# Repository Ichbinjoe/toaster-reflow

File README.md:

# Toaster Reflow

This board is a Raspberry Pi hat designed to be hooked up to a toaster oven to
reflow circuit boards. This board features:

+ AC Relay for turning on and off the toaster oven
+ Two thermocouple inputs
+ A servo connection for optional door servo
+ A buzzer for notifications

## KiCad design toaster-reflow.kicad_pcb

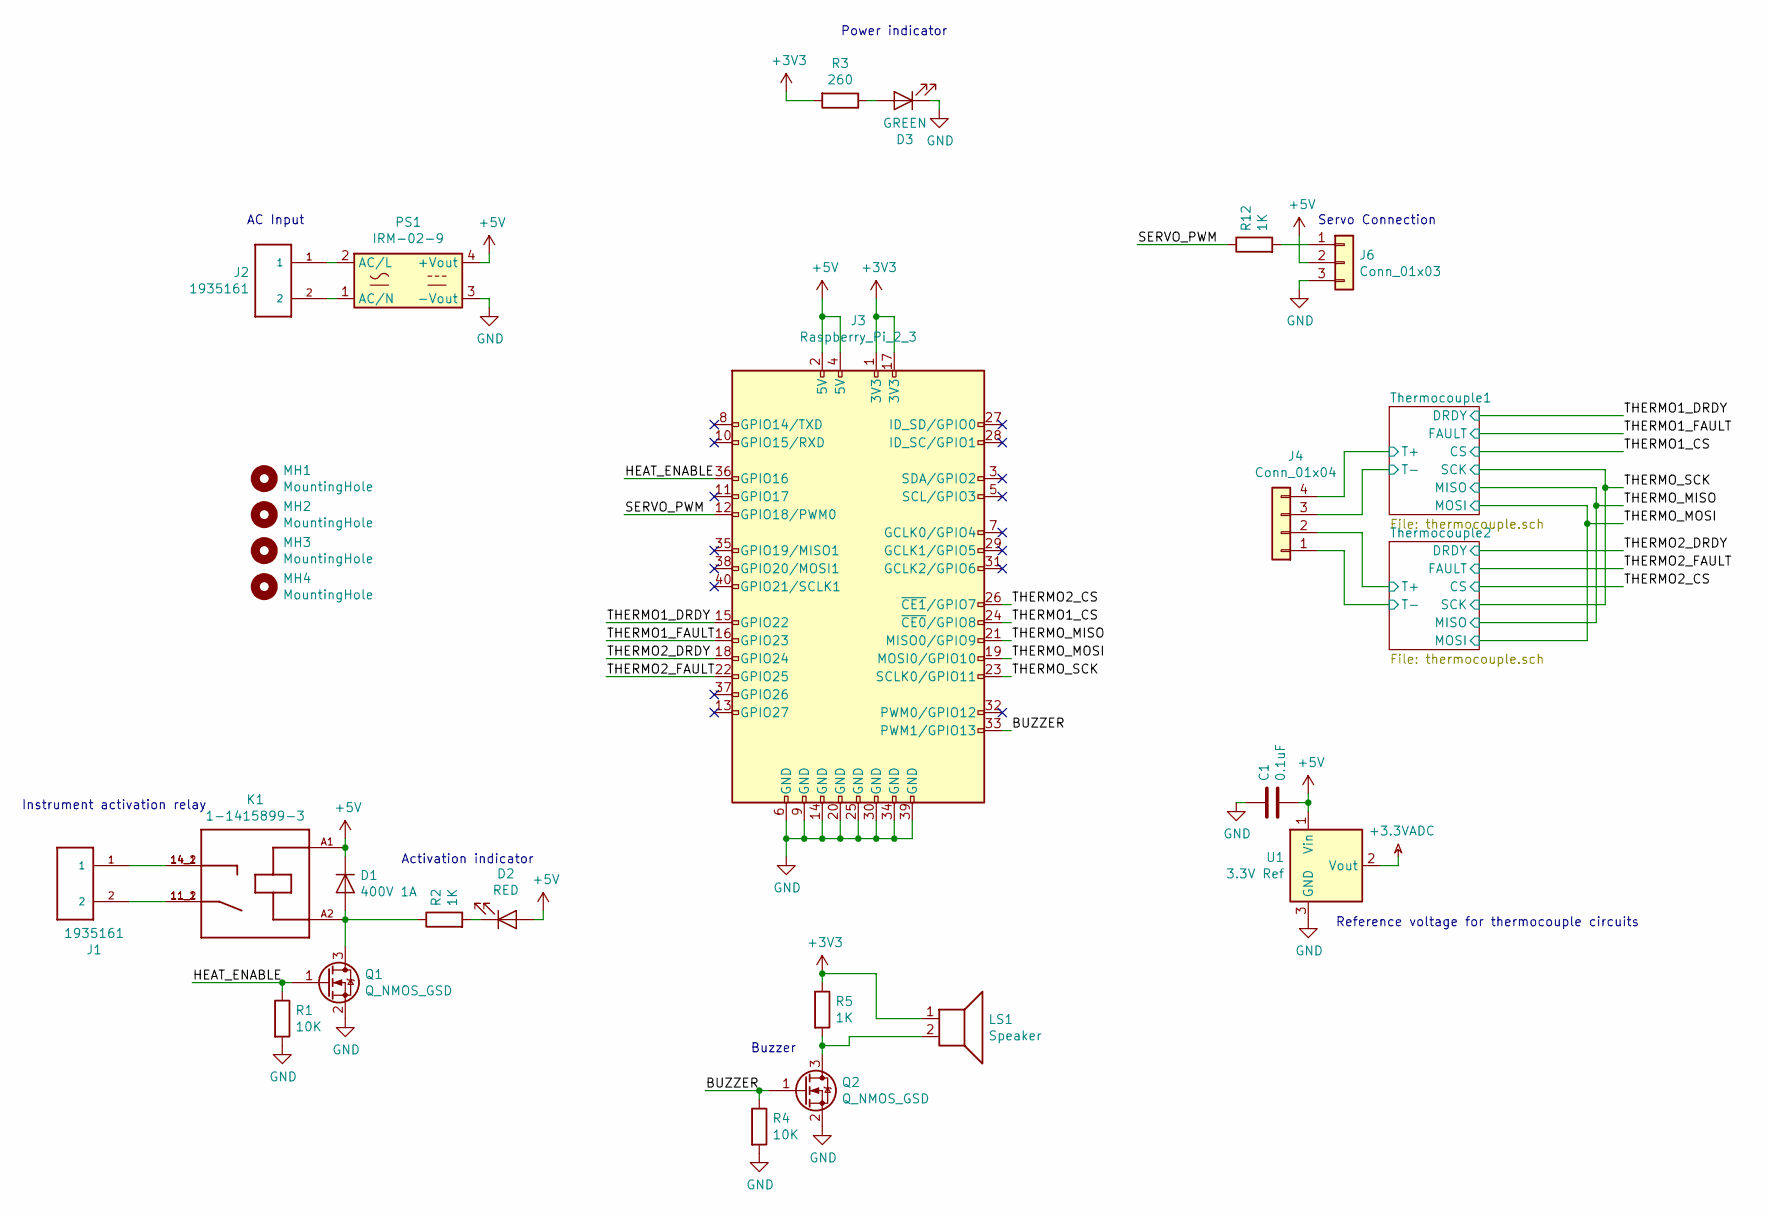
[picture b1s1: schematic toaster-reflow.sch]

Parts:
C1: 0.1uF; C_0603_1608Metric; DigikeyPartNumber 1276-1258-1-ND
D1: 400V 1A; D_SMA; DigikeyPartNumber 1655-1504-1-ND
D2: RED; D_0603_1608Metric; DigikeyPartNumber 732-4978-1-ND
D3: GREEN; D_0603_1608Metric; DigikeyPartNumber 732-4980-1-ND
J1, J2: 1935161; PHOENIX_1935161; DigikeyPartNumber 277-1667-ND
J3: Raspberry_Pi_2_3; PinHeader_2x20_P2.54mm_Vertical; DigikeyPartNumber S9200-ND
J4: Conn_01x04; 1990025; DigikeyPartNumber 277-1796-ND
J6: Conn_01x03; PinSocket_1x03_P2.54mm_Vertical; DigikeyPartNumber 732-5316-ND
K1: 1-1415899-3; RELAY_1-1415899-3; DigikeyPartNumber PB1267-ND
LS1: Speaker; PS12; DigikeyPartNumber 445-2525-1-ND
MH1, MH2, MH3, MH4: MountingHole; MountingHole_2.7mm_M2.5; DigikeyPartNumber 732-12923-ND
PS1: IRM-02-9; IRM-15-5; DigikeyPartNumber 1866-3037-ND
Q1, Q2: Q_NMOS_GSD; SC-59; DigikeyPartNumber RK7002BMT116CT-ND
R1, R4: 10K; R_0603_1608Metric; DigikeyPartNumber P10KGCT-ND
R2, R5, R12: 1K; R_0603_1608Metric; DigikeyPartNumber RHM1.0KDCT-ND
R3: 260; R_0603_1608Metric; DigikeyPartNumber P261HCT-ND
U1: 3.3V Ref; SOT-23; DigikeyPartNumber NCP51460SN33T1GOSCT-ND

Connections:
+3.3VADC: U1.2 (Vout); also elsewhere on the board
+3V3: J3.1 (3V3), J3.17 (3V3), LS1.1, R3.2, R5.1; also elsewhere on the board
+5V: C1.2, D1.1 (K), D2.2 (A), J3.2 (5V), J3.4 (5V), J6.2, K1.A1 (A2), PS1.4 (+Vout), U1.1 (Vin)
/BUZZER: J3.33 (PWM1/GPIO13), Q2.1 (G), R4.1
/HEAT_ENABLE: J3.36 (GPIO16), Q1.1 (G), R1.1
/SERVO_PWM: J3.12 (GPIO18/PWM0), R12.1
/THERMO1_CS: J3.24 (~CE0~/GPIO8); also elsewhere on the board
/THERMO1_DRDY: J3.15 (GPIO22); also elsewhere on the board
/THERMO1_FAULT: J3.16 (GPIO23); also elsewhere on the board
/THERMO2_CS: J3.26 (~CE1~/GPIO7); also elsewhere on the board
/THERMO2_DRDY: J3.18 (GPIO24); also elsewhere on the board
/THERMO2_FAULT: J3.22 (GPIO25); also elsewhere on the board
/THERMO_MISO: J3.21 (MISO0/GPIO9); also elsewhere on the board
/THERMO_MOSI: J3.19 (MOSI0/GPIO10); also elsewhere on the board
/THERMO_SCK: J3.23 (SCLK0/GPIO11); also elsewhere on the board
/Thermocouple1/T+: J4.4; also elsewhere on the board
/Thermocouple1/T-: J4.3; also elsewhere on the board
/Thermocouple2/T+: J4.2; also elsewhere on the board
/Thermocouple2/T-: J4.1; also elsewhere on the board
GND: C1.1, D3.1 (K), J3.6 (GND), J3.9 (GND), J3.14 (GND), J3.20 (GND), J3.25 (GND), J3.30 (GND), J3.34 (GND), J3.39 (GND), J6.3, PS1.3 (-Vout), Q1.2 (S), Q2.2 (S), R1.2, R4.2, U1.3 (GND); also elsewhere on the board
unnamed: D1.2 (A), K1.A2 (A1), Q1.3 (D), R2.1
unnamed: D2.1 (K), R2.2
unnamed: D3.2 (A), R3.1
unnamed: J1.1, K1.14_1 (14), K1.14_2 (14)
unnamed: J1.2, K1.11_1 (11), K1.11_2 (11)
unnamed: J2.1, PS1.2 (AC/L)
unnamed: J2.2, PS1.1 (AC/N)
unnamed: J6.1, R12.2
unnamed: LS1.2, Q2.3 (D), R5.2

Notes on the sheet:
Power indicator
Activation indicator
Instrument activation relay
Servo Connection
Reference voltage for thermocouple circuits
Buzzer
AC Input

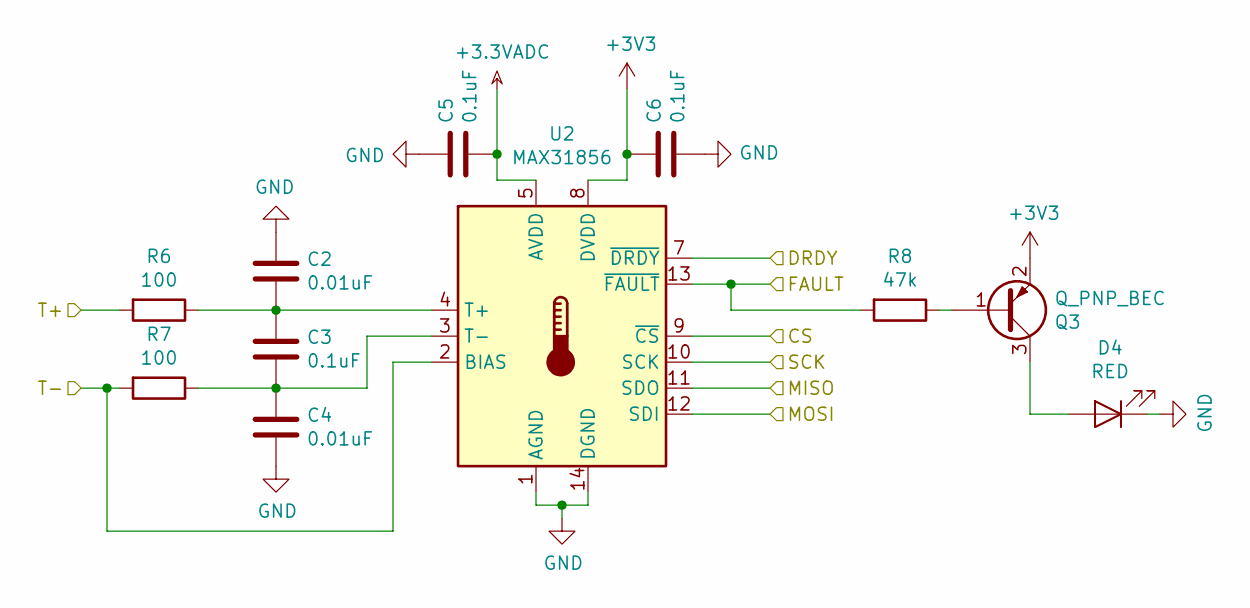
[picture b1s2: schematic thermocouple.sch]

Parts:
C2, C4: 0.01uF; C_0603_1608Metric; DigikeyPartNumber 1276-1921-1-ND
C3, C5, C6: 0.1uF; C_0603_1608Metric; DigikeyPartNumber 1276-1258-1-ND
D4: RED; D_0603_1608Metric; DigikeyPartNumber 732-4978-1-ND
Q3: Q_PNP_BEC; SC-59; DigikeyPartNumber MMBT3906-FDICT-ND
R6, R7: 100; R_0603_1608Metric; DigikeyPartNumber P100HCT-ND
R8: 47k; R_0603_1608Metric; DigikeyPartNumber P47.0KHCT-ND
U2: MAX31856; TSSOP-14_4.4x5mm_P0.65mm; DigikeyPartNumber MAX31856MUD+-ND

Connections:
+3.3VADC: C5.2, U2.5 (AVDD); also elsewhere on the board
+3V3: C6.1, Q3.2 (E), U2.8 (DVDD); also elsewhere on the board
/THERMO1_CS: U2.9 (~CS); also elsewhere on the board
/THERMO1_DRDY: U2.7 (~DRDY); also elsewhere on the board
/THERMO1_FAULT: R8.2, U2.13 (~FAULT); also elsewhere on the board
/THERMO_MISO: U2.11 (SDO); also elsewhere on the board
/THERMO_MOSI: U2.12 (SDI); also elsewhere on the board
/THERMO_SCK: U2.10 (SCK); also elsewhere on the board
/Thermocouple1/T+: R6.2; also elsewhere on the board
/Thermocouple1/T-: R7.2, U2.2 (BIAS); also elsewhere on the board
GND: C2.1, C4.2, C5.1, C6.2, D4.1 (K), U2.1 (AGND), U2.14 (DGND); also elsewhere on the board
unnamed: C2.2, C3.1, R6.1, U2.4 (T+)
unnamed: C3.2, C4.1, R7.1, U2.3 (T-)
unnamed: D4.2 (A), Q3.3 (C)
unnamed: Q3.1 (B), R8.1

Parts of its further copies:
C7, C9: 0.01uF; C_0603_1608Metric; DigikeyPartNumber 1276-1921-1-ND
C8, C10, C11: 0.1uF; C_0603_1608Metric; DigikeyPartNumber 1276-1258-1-ND
D5: RED; D_0603_1608Metric; DigikeyPartNumber 732-4978-1-ND
Q4: Q_PNP_BEC; SC-59; DigikeyPartNumber MMBT3906-FDICT-ND
R9, R10: 100; R_0603_1608Metric; DigikeyPartNumber P100HCT-ND
R11: 47k; R_0603_1608Metric; DigikeyPartNumber P47.0KHCT-ND
U3: MAX31856; TSSOP-14_4.4x5mm_P0.65mm; DigikeyPartNumber MAX31856MUD+-ND

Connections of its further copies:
+3.3VADC: C10.2, U3.5 (AVDD); also elsewhere on the board
+3V3: C11.1, Q4.2 (E), U3.8 (DVDD); also elsewhere on the board
/THERMO2_CS: U3.9 (~CS); also elsewhere on the board
/THERMO2_DRDY: U3.7 (~DRDY); also elsewhere on the board
/THERMO2_FAULT: R11.2, U3.13 (~FAULT); also elsewhere on the board
/THERMO_MISO: U3.11 (SDO); also elsewhere on the board
/THERMO_MOSI: U3.12 (SDI); also elsewhere on the board
/THERMO_SCK: U3.10 (SCK); also elsewhere on the board
/Thermocouple2/T+: R9.2; also elsewhere on the board
/Thermocouple2/T-: R10.2, U3.2 (BIAS); also elsewhere on the board
GND: C7.1, C9.2, C10.1, C11.2, D5.1 (K), U3.1 (AGND), U3.14 (DGND); also elsewhere on the board
unnamed: C7.2, C8.1, R9.1, U3.4 (T+)
unnamed: C8.2, C9.1, R10.1, U3.3 (T-)
unnamed: D5.2 (A), Q4.3 (C)
unnamed: Q4.1 (B), R11.1

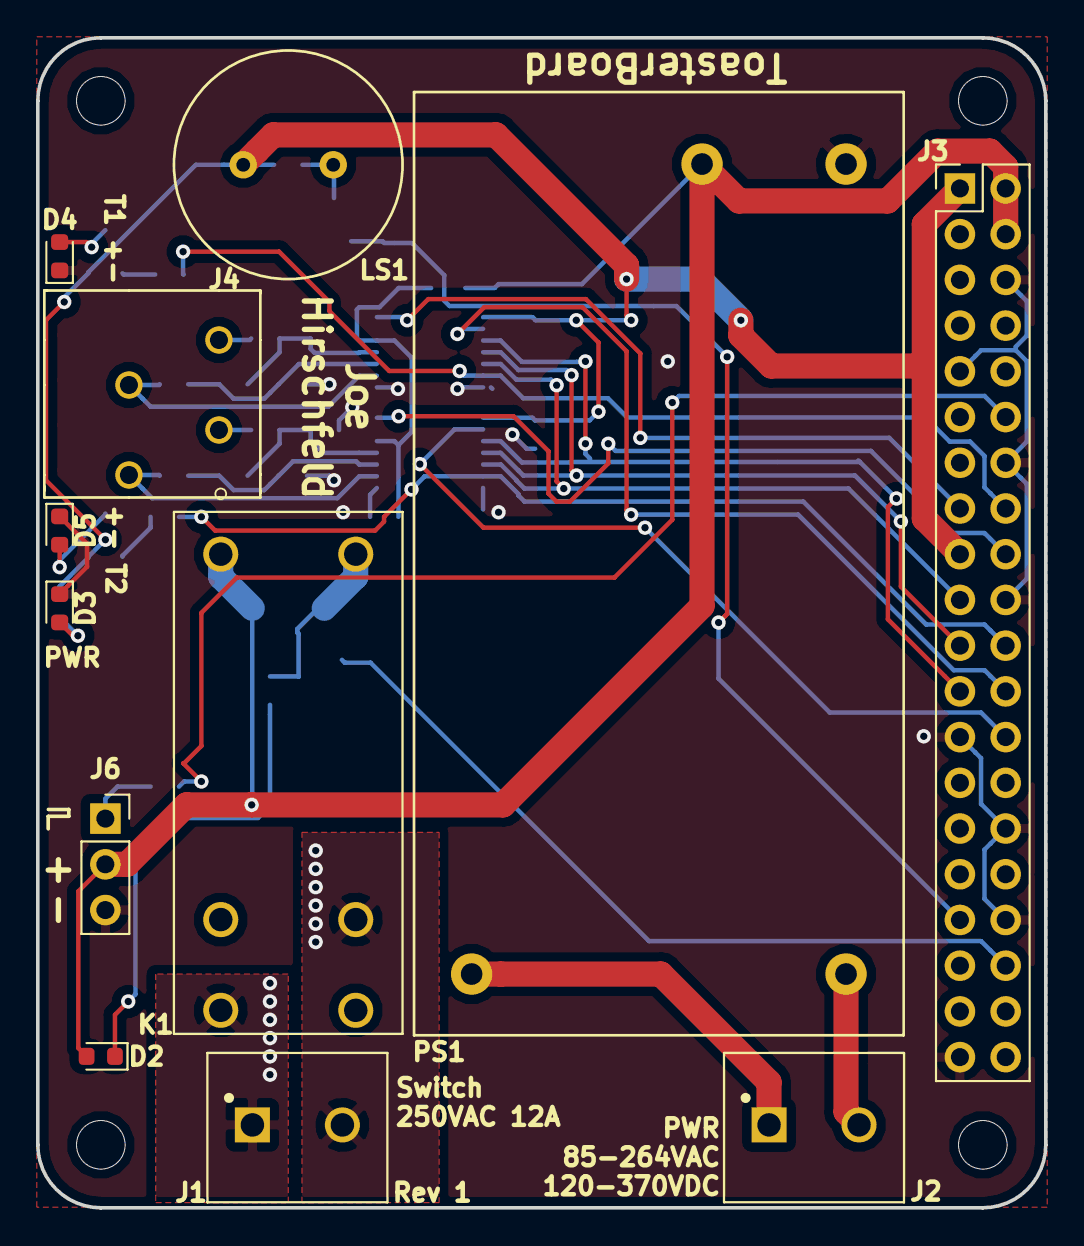
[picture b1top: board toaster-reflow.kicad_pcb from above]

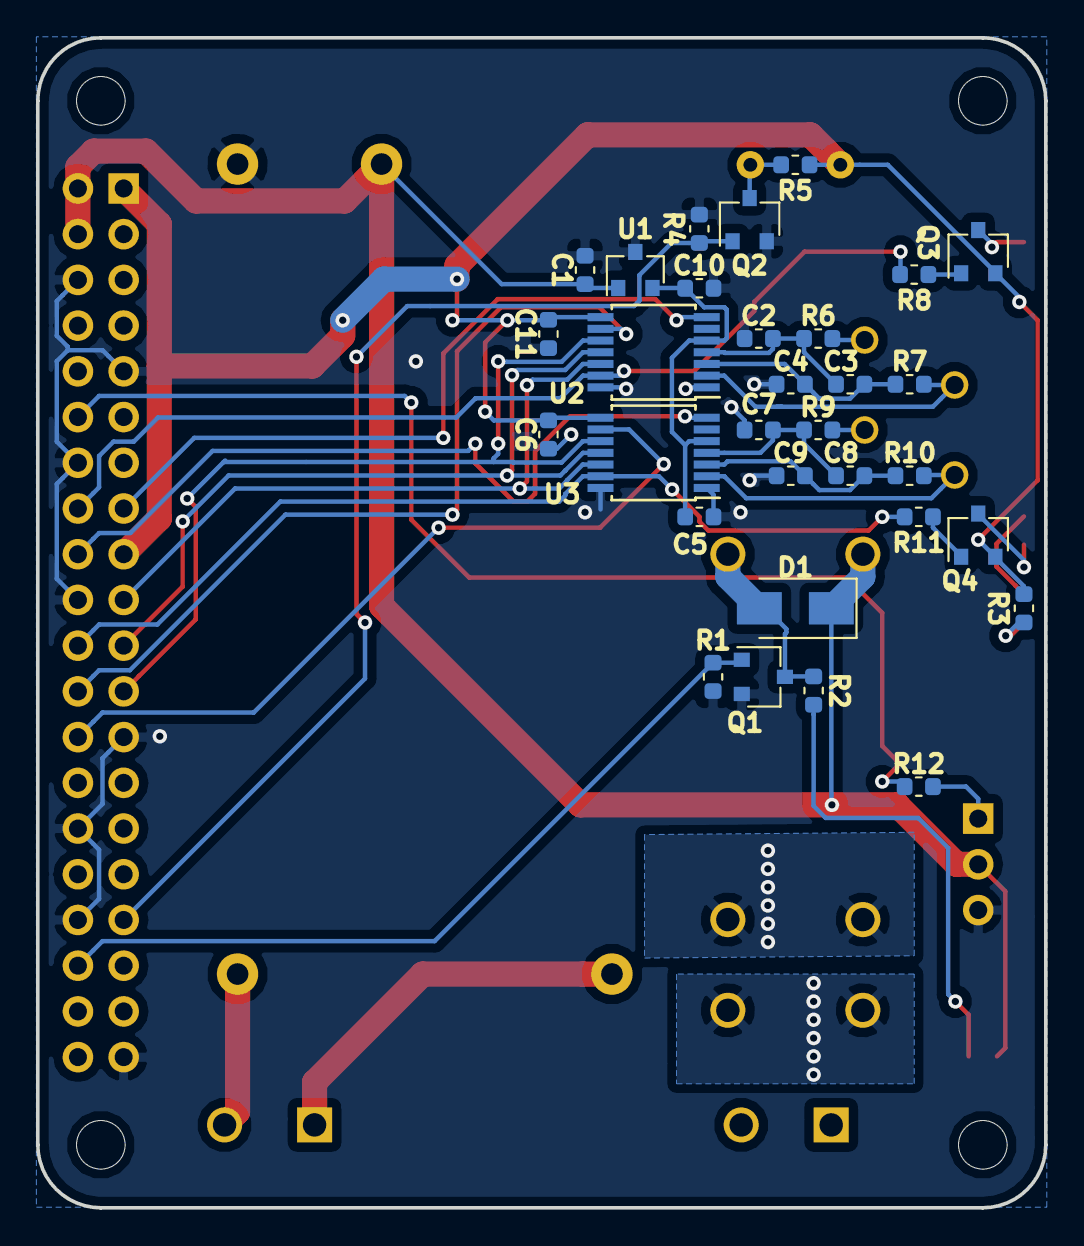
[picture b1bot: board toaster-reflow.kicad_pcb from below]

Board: 2 copper layers, 56.0 x 65.0 mm, 47 parts (31 on the bottom side), 37 nets.

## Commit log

2018-08-31 Add bom wizard, fix 'duplicate' part
2018-09-01 Use better MAX31856, fill in some parts
2018-09-01 Add pcb, update packages
2018-09-01 Forgot a footprint! Created components on board
2018-09-01 Finish pcb routing
2018-09-01 move some silkscreen items
2018-09-20 update pcb
2018-09-21 Add a bunch of stuff
2018-09-21 update pcb for 3d rendering
2018-10-11 UPdate transistor wiring
2018-11-06 update some stuff
2018-11-06 new design/ layout
2018-11-07 update some silkscreening
2018-11-07 send out for fabrication
